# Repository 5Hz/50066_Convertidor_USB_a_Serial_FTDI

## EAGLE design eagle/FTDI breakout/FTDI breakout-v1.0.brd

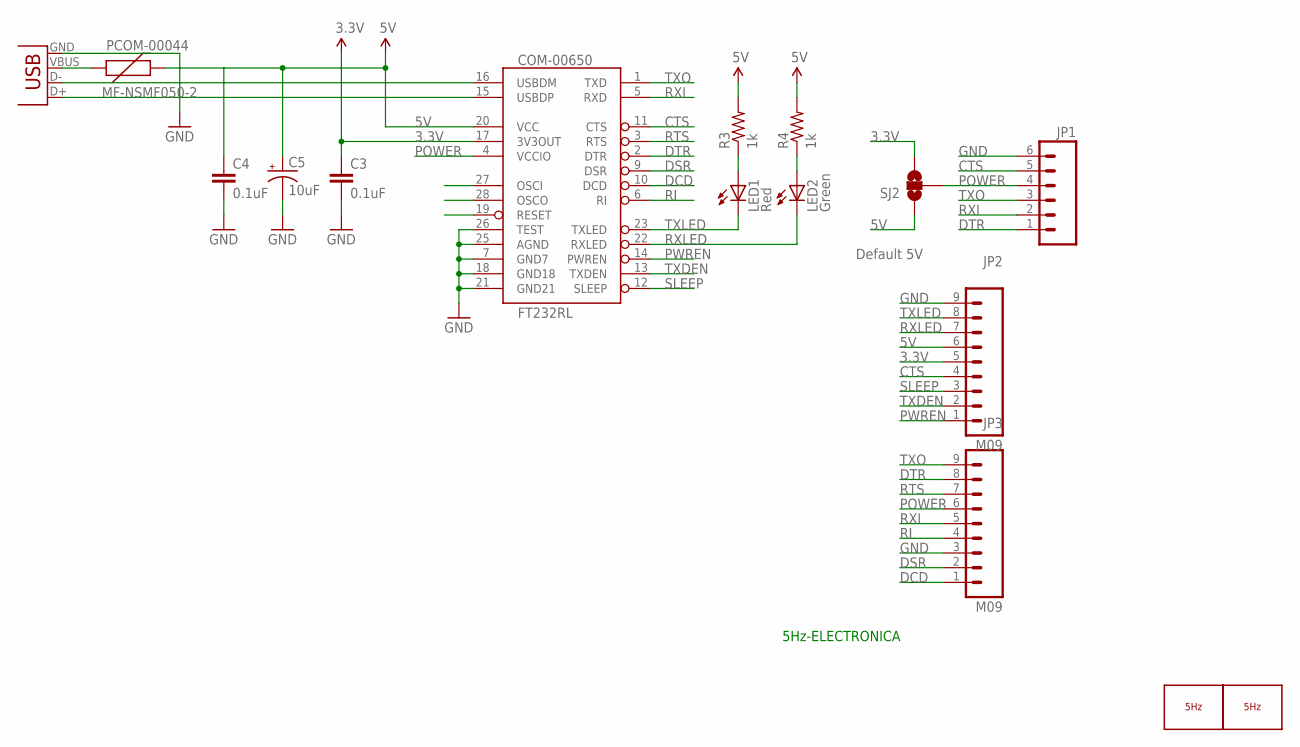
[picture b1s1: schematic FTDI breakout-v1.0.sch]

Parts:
C3, C4: 0.1uF; 0603-CAP
C5: 10uF; EIA3216
COM-00650: FT232RL; SSOP28DB
JP1: M06SIP; 1X06
JP2, JP3: M09; 1X09
LED1: Red; LED-0603
LED2: Green; LED-0603
LOGO1: LOGO_5HZ_H_5MM; 5HZ_LOGO_H_5MM
LOGO2: LOGO_5HZ_H_15MM; 5HZ_LOGO_H_15MM
PCOM-00044: MF-NSMF050-2; PTC-1206
PRT-00587: 897-43-005-00-100001; USB-MINIB
R3, R4: 1k; 0603-RES
SJ2: SOLDERJUMPER_2WAYS; SJ_3

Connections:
3.3V: C3.1, COM-00650.17 (3V3OUT), JP2.5, SJ2.3
5V: C4.1, C5.A (+), COM-00650.20 (VCC), JP2.6, PCOM-00044.2, R3.2, R4.2, SJ2.1
CTS: COM-00650.11 (CTS), JP1.5, JP2.4
DCD: COM-00650.10 (DCD), JP3.1
DSR: COM-00650.9 (DSR), JP3.2
DTR: COM-00650.2 (DTR), JP1.1, JP3.8
GND: C3.2, C4.2, C5.C (-), COM-00650.7 (GND7), COM-00650.18 (GND18), COM-00650.21 (GND21), COM-00650.25 (AGND), COM-00650.26 (TEST), JP1.6, JP2.9, JP3.3, PRT-00587.GND
unnamed: LED1.A, R3.1
unnamed: LED2.A, R4.1
unnamed: PCOM-00044.1, PRT-00587.VBUS
POWER: COM-00650.4 (VCCIO), JP1.4, JP3.6, SJ2.2
PWREN: COM-00650.14 (PWREN), JP2.1
RI: COM-00650.6 (RI), JP3.4
RTS: COM-00650.3 (RTS), JP3.7
RXI: COM-00650.5 (RXD), JP1.2, JP3.5
RXLED: COM-00650.22 (RXLED), JP2.7, LED2.C
SLEEP: COM-00650.12 (SLEEP), JP2.3
TXDEN: COM-00650.13 (TXDEN), JP2.2
TXLED: COM-00650.23 (TXLED), JP2.8, LED1.C
TXO: COM-00650.1 (TXD), JP1.3, JP3.9
USB_D+: COM-00650.15 (USBDP), PRT-00587.D+
USB_D-: COM-00650.16 (USBDM), PRT-00587.D-

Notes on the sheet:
Default 5V
5Hz-ELECTRONICA

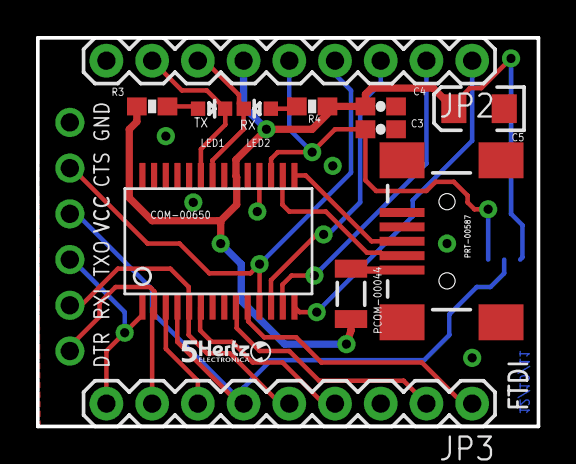
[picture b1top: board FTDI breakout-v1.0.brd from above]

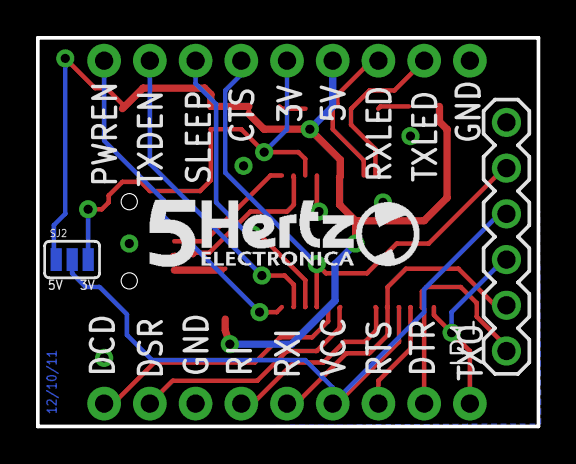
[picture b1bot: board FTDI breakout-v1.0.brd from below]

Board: 2 copper layers, 27.8 x 21.6 mm, 16 parts (3 on the bottom side), 22 nets.

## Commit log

2014-01-13 creación
